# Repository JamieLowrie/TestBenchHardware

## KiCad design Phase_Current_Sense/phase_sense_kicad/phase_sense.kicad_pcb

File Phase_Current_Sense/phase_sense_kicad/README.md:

# 3-Channel Motor Phase Current + Voltage Sense — ACS37002 (KiCad 7 project), rev H — 4 layers

Open `phase_sense.kicad_pro` in KiCad 7, 8 or 9 (8/9 will offer to upgrade the files).

## What it is
- 3 × Allegro ACS37002LMABTR-066B3 (LCSC C3684355): ±66.7 A, 19.8 mV/A, 1.65 V = 0 A, 3.3 V supply
- 3 × phase-voltage dividers: 47k + 47k (C25819, two in series for voltage rating) / 2.7k (C13167) with 22 nF (C21122),
  tapped on the **motor side** of each sensor
- Each phase passes through two XFCN T44001 M4 solder terminals (LCSC C481447, 40 A, 4 legs): **IN (from drive) → sensor → OUT (to motor)**
- **4 layers**, board = CamdenBoss **CDIB/6/L2** lower PCB: 99.0 × 82.8 mm, 1 mm corner chamfers (from `CDIB-6ST-L2.STEP`)

## Layout — rev F
- The sensor circuit is pushed as far right as it goes. **The controller gets X < 53.6 mm** (dashed line on silk). Only J1
  and its little ground pad (X 47.4–55.3, Y 44–68.4, with Q1, R2, R3 and R4) stick over the line, as the interface.
- **Top-right window (Y < 10.5), from the middle outwards: DC− (J8, X 64.0), C IN 73.5, B IN 83.0, A IN 94.2.**
- **Bottom-right window (Y > 72.3): C OUT 65.5, B OUT 80.0, A OUT 94.2.**
- Each phase is one strip, C | B | A from left to right: IN terminal → sensor pins 1–4 (IP+) → pins 5–8 (IP−) → OUT terminal.
- **Layer use:**
  - **F.Cu / B.Cu:** phase copper on both layers, via-stitched, plus the small parts and GND.
  - **In1.Cu:** the LV signal wiring. It crosses under the phase strips only in a via-free band (Y 51.0–58.2).
  - **In2.Cu:** GND only. It sits under the LV areas, the crossing band, J1 and a strip from DC− down to J1. It is kept out from under the
    phase copper, so the phase dv/dt doesn't couple into GND.
- The A IN copper splits around the H2 pillar screw. It keeps 4 mm clear on top (under the screw head) and 2.4 mm clear on B.Cu.
  That still leaves about 5 mm on F.Cu and about 8.5 mm on B.Cu past the screw.

## Gain select — driven by the MCU
The GAIN_SEL pins of all three sensors are bussed and brought to J1:
- **GS0** goes to every sensor's GAIN_SEL_0 (pin 16), through R3 (10 kΩ).
- **GS1** goes to every sensor's GAIN_SEL_1 (pin 14), through R4 (10 kΩ).
- Inside each sensor there is a 1 MΩ pull-down, so a floating or reset GPIO gives **00**.

| GS1 / GS0 | Sensitivity | Range | Current per ADC count |
|---|---|---|---|
| 0 0 (default) | 19.8 mV/A | ±66.7 A | ~41 mA |
| 0 1 | 16.5 mV/A | ±80 A | ~49 mA |
| 1 0 | 13.2 mV/A | ±100 A | ~61 mA |
| 1 1 | 9.9 mV/A | ±133.3 A | ~81 mA |

**The ACS37002 only reads GAIN_SEL when it powers up**, so changing GS0/GS1 while it runs does nothing. To make a new
setting take effect, the board switches the sensors' supply:
- **Q1 (AO3401A, P-channel MOSFET)** feeds the sensors from +3V3 on a separate rail, **+3.3VA**.
- **R2** holds Q1 on, so the sensors run as soon as the board is powered.
- **SNS_OFF (J1 pin 13)**: drive it high to switch the sensors off.

Change the range from firmware like this:
1. Set GS0 / GS1 to the new code (push-pull outputs).
2. Drive SNS_OFF **high** for at least 10 ms. The sensors power down and +3.3VA falls below the power-on-reset level.
3. Drive SNS_OFF **low**. The sensors restart and latch the new GAIN_SEL.
4. Wait about 1 ms, then re-measure the zero-current offset and change the firmware scale.
5. Ignore FAULT_N and the ADC readings while the sensors are off (FAULT_N reads low then).

The overcurrent trip set by the VOC divider is a fraction of the selected range, so it moves up with the range. Check the
ACS37002 datasheet's VOC equation if you rely on FAULT_N at the higher ranges.

Why R3/R4 are there: while +3.3VA is off, a GPIO held high would feed the sensors through their input protection diodes.
That could stop them resetting properly. 10 kΩ limits it to a fraction of a milliamp. At 3.3 V the pin still sees about 3.2 V,
well above the 2.25 V logic-high threshold.

The VOC overcurrent trip divider and the FAULT_N pull-up sit on +3.3VA. Q1 drops about 3 mV, which slightly offsets the
ratiometric output (3.3 V seen by the MCU's ADC vs. ~3.297 V at the sensors). The firmware zero-calibration absorbs it.

## Current sign
Drive → motor current enters IP+, so it reads **positive**: `I = (adc − zero) × (3.3 / 4096) / 0.0198` → ≈ 40.7 mA/count.

## J1 – interface header (2.54 mm, 2×7) at X 51.0 / 53.54, Y 50.6–65.8
Wire these nets to the CH32V203 on your controller layout, or keep J1 as a header. Pin 1 is the square pad (top-left);
odd pins in the left column, even pins in the right. The pinout is printed on the back.

| Pin | Signal | Notes |
|---|---|---|
| 1 | 3V3 | MCU 3.3 V in. Same rail as MCU VDDA (the current output is ratiometric). Feeds the sensors through Q1 |
| 2 | IA | Phase A current, RC-filtered (1 kΩ / 10 nF, fc ≈ 16 kHz) → ADC |
| 3 | IB | Phase B current → ADC |
| 4 | IC | Phase C current → ADC |
| 5 | VA | Phase A voltage (÷35.8, fc ≈ 2.8 kHz) → ADC |
| 6 | VB | Phase B voltage → ADC |
| 7 | VC | Phase C voltage → ADC |
| 8 | FAULT_N | Open-drain wired-OR of all three OCF pins, 10 k pull-up to +3.3VA, active low (~77 A at the default range) |
| 9, 10, 14 | GND | |
| 11 | GS0 | GAIN_SEL_0 of all three sensors (GPIO out) |
| 12 | GS1 | GAIN_SEL_1 of all three sensors (GPIO out) |
| 13 | SNS_OFF | High = sensors off (GPIO out). Low or floating = sensors on |

Voltage: `V = adc × (3.3 / 4096) × (96.7 / 2.7)` → ≈ 28.9 mV/count, 118 V full scale (100 V → 2.79 V).

## J8 – drive DC− link (required for VA/VB/VC)
Phase voltage is measured relative to the drive's DC−. Bolt J8 to the drive's DC− with a short wire.
**This ties board GND (and your CH32V203, USB and debugger ground) to the drive's DC−**, so the board is not isolated
from the motor supply. Max bus voltage 100 V.

## Box fit (CDIB/6/L2), all in board coordinates (X right, Y down from the top window)
- **H1 (6.995, 66.405) and H2 (91.995, 16.405)**: Ø3.6 mm holes onto the two pillars, fixed with **No.6 self-tapping screws**.
- Terminal legs are only in the two open wiring strips (5.7 mm of space below the board there).
- **Centre platform, Y 21.5–61.2: only 0.5 mm below the PCB.** Everything there is SMD except **J1. Cut its legs flush**, or
  fit a surface-mount header.
- Box centre posts (X 45.7–53.2 at both ends) leave 3.3 mm above the board. Only flat copper is under them.
- About 19.5 mm from the PCB top to the roof: T44001 (8.4 mm) + ring lug + M4 pan head fits. Use ≤ 8 mm M4 screws.

## Spacing / creepage
- Custom DRC rule (`phase_sense.kicad_dru`): **every phase net keeps ≥ 0.5 mm from every other net**. That covers LV tracks, GND and the
  other phases (IPC-2221 B4, solder-masked, ≤ 100 V, with margin). Phase-to-phase copper gaps are 0.8 mm. The GND pour
  respects the rule when it is filled.
- The divider chains deliberately bridge HV to LV (47k + 47k), and J8 ties GND to DC−, so the board is **not** galvanically isolated.
- The ACS37002 package itself keeps ~7 mm between its HV and LV pins (1097 Vrms basic insulation working voltage).

## Known limitations — read before ordering
- **Current:** each sensor's primary is 0.85 mΩ, so 60 A DC ≈ 3 W per chip, which is too much for SOIC-16 continuously.
  **~30 A RMS per phase is the practical continuous limit. Order 2 oz outer copper.** The narrowest spot is A IN past
  the H2 screw (about 5 mm on F.Cu plus 8.5 mm on B.Cu).
- **Field coupling:** each phase's own OUT copper runs down right beside its sensor, and the next phase is one strip away.
  The ACS37002 rejects uniform external fields, but check each channel once against a clamp meter. If it is off by more than ~1 %,
  store a per-channel gain in firmware.

## Ordering at JLCPCB
1. Upload `fab/gerbers_JLCPCB.zip`. **4 layers, 1.6 mm, 2 oz outer copper** (the inner layers can stay at 0.5 oz; they carry no phase current).
2. PCB Assembly, top side: upload `fab/BOM_JLCPCB.csv` + `fab/CPL_JLCPCB.csv`.
3. **Check U1–U3 rotation in JLC's placement preview**: the pin-1 dot must be top-left, toward the IN terminals.
   KiCad and JLC sometimes disagree on SOIC rotation; fix it in the preview if needed.
4. J2–J8 (T44001) are through-hole. Either use JLC THT assembly, or remove them from the BOM and hand-solder with a big iron
   (≥ 80 W). The pours sink a lot of heat.
5. J1 is not in the BOM. Fit it yourself and trim the legs flush (see box notes).

## Verification done
- Schematic netlist cross-checked against the design (129 pins, 0 errors).
- PCB DRC: 0 unconnected, 0 clearance, 0 courtyard errors, with the 0.5 mm phase rule active. The only remaining entries are
  "library not in configuration" warnings from the headless build machine.
- Every PCB pad net and footprint matches the schematic (0 mismatches).

`gen/` holds the Python scripts that generated everything (`run.sh` = place + autoroute + DRC, `fab.py` = outputs).

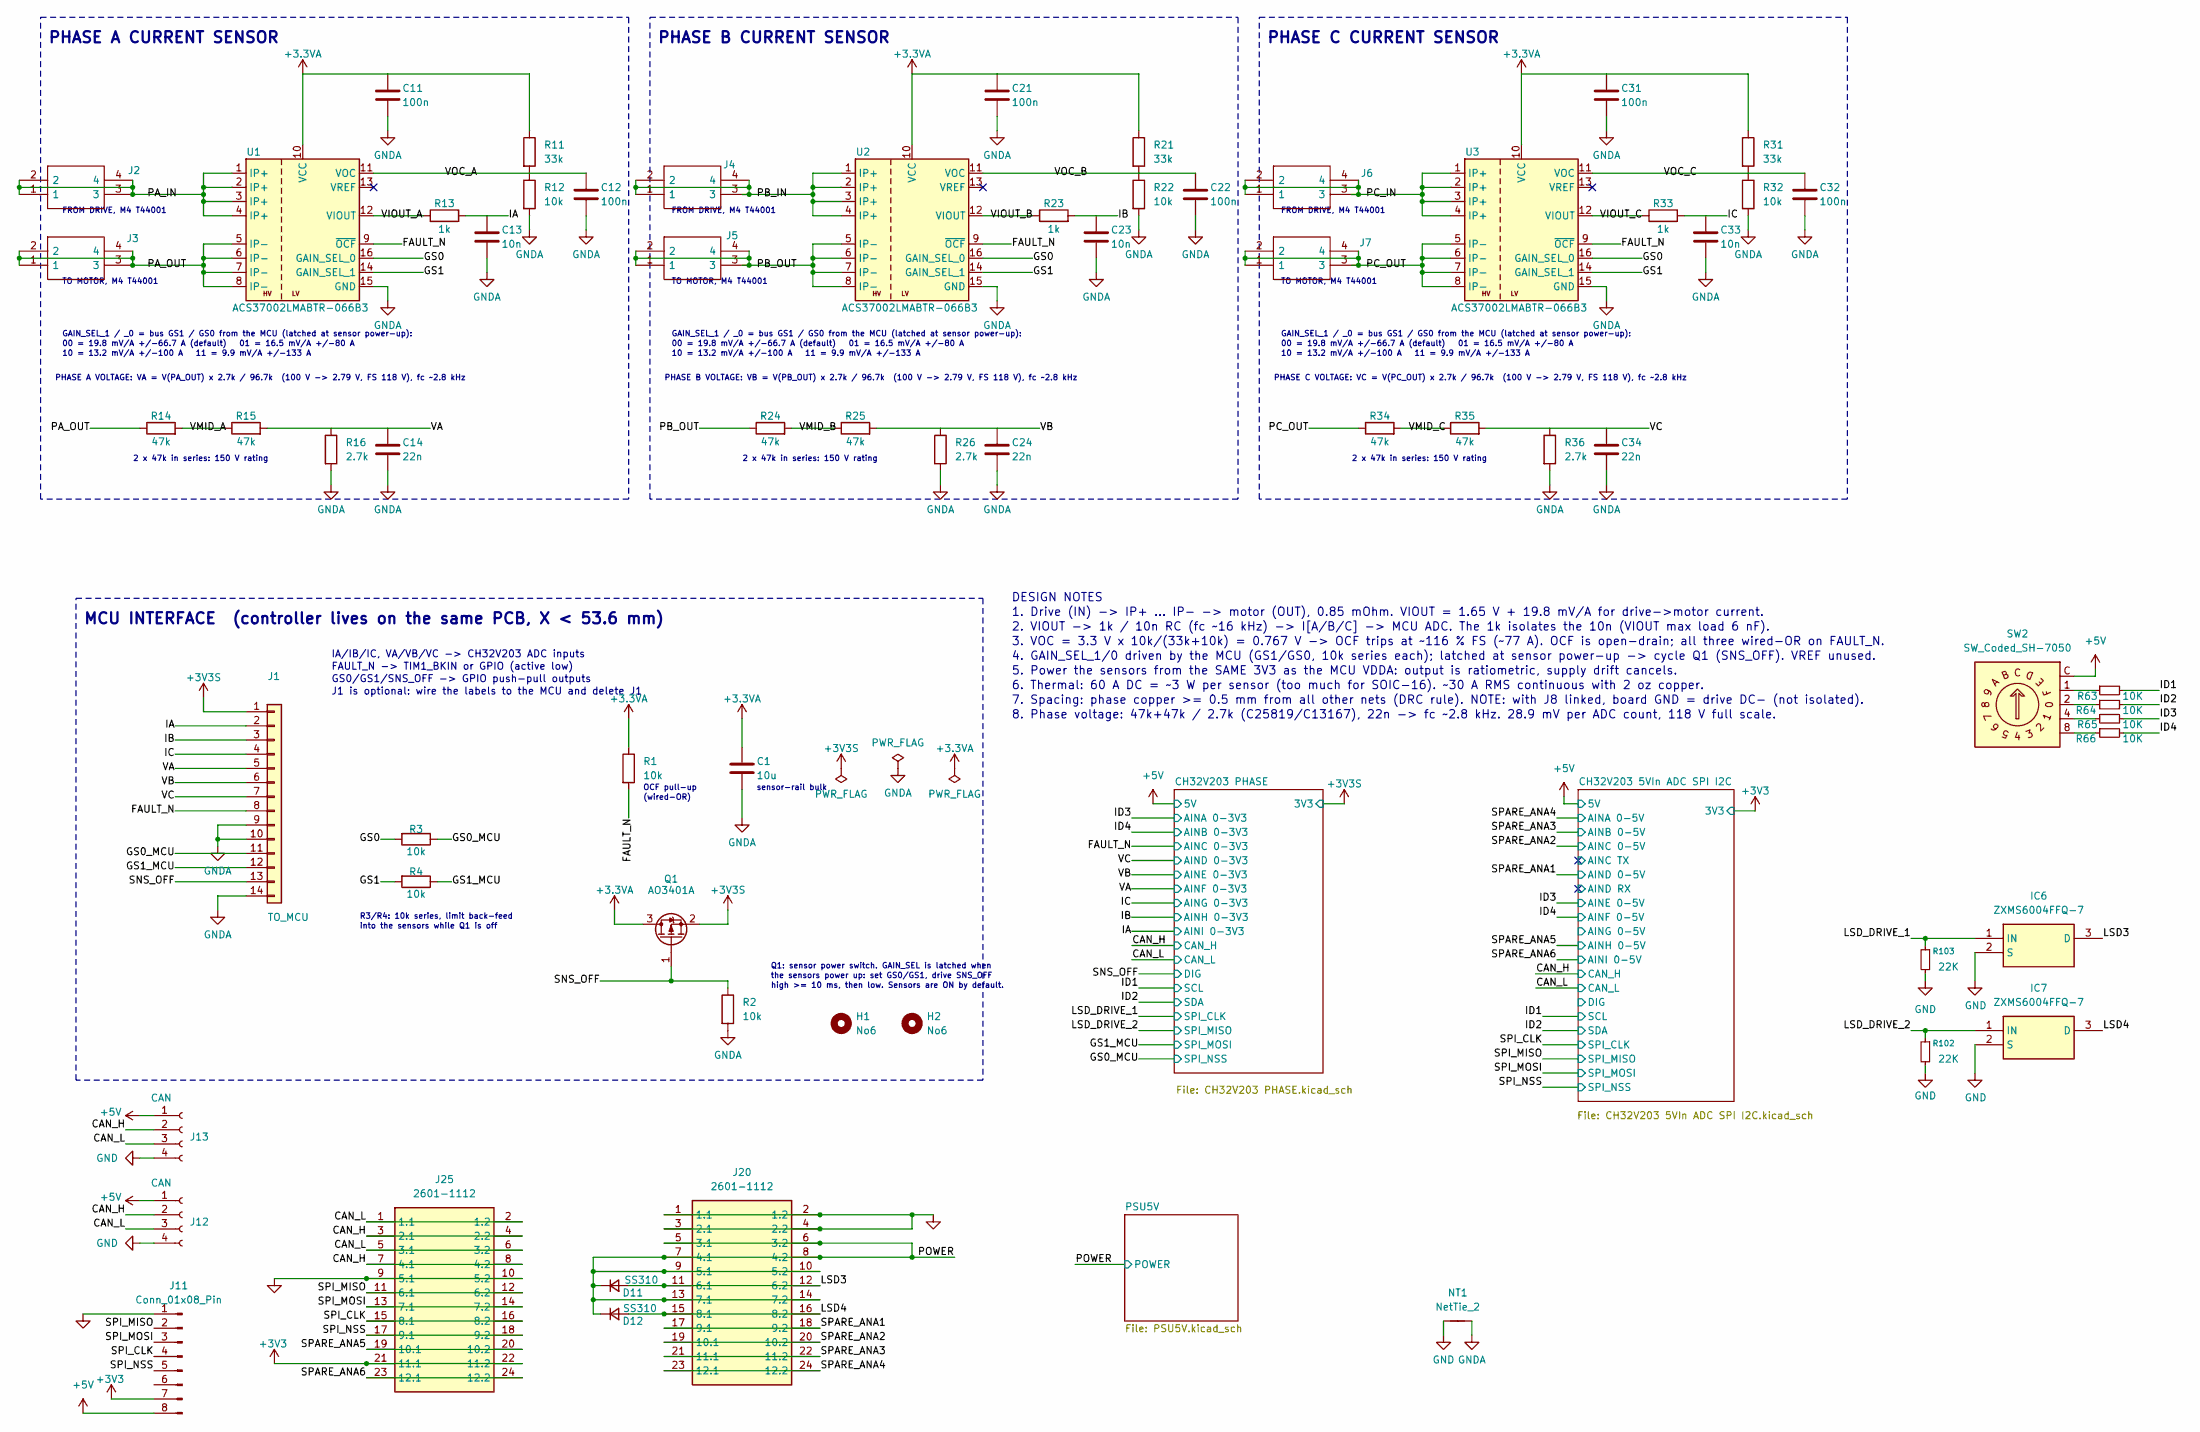
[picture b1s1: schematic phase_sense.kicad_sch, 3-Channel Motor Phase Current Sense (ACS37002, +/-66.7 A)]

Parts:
C1: 10u; C_0603_1608Metric; LCSC C19702
C11, C12, C21, C22, C31, C32: 100n; C_0603_1608Metric; LCSC C14663
C13, C23, C33: 10n; C_0603_1608Metric; LCSC C57112
C14, C24, C34: 22n; C_0603_1608Metric; LCSC C21122
D11, D12: SS310; D_SMA; LCSC DESCRIPTION 100V 3A Schottky Diode, SMA
H1, H2: No6; CDIB_Pillar_No6_Screw
IC6, IC7: ZXMS6004FFQ-7; SOTFL95P240X110-3N; Manufacturer_Part_Number ZXMS6004FFQ-7; Mouser Part Number 621-ZXMS6004FFQ-7
J1: TO_MCU; PinHeader_2x07_P2.54mm_Vertical
J2, J3, J4, J5, J6, J7: AMT0440007DB0000G; Manufacturer_Part_Number AMT0440007DB0000G; Mouser Part Number 523-AMT0440007DB000G
J11: Conn_01x08_Pin; JST_GH_BM09B-GHS-TBT_1x09-1MP_P1.25mm_Vertical; LCSC DNF
J12, J13: CAN; JST_GH_BM04B-GHS-TBT_1x04-1MP_P1.25mm_Vertical; LCSC DNF
J20, J25: 2601-1112; 26011112; Manufacturer_Part_Number 2601-1112
NT1: NetTie_2; NetTie-2_THT_Pad1.0mm
Q1: AO3401A; SOT-23; LCSC C15127
R1, R2, R3, R4, R12, R22, R32: 10k; R_0603_1608Metric; LCSC C25804
R11, R21, R31: 33k; R_0603_1608Metric; LCSC C4216
R13, R23, R33: 1k; R_0603_1608Metric; LCSC C21190
R14, R15, R24, R25, R34, R35: 47k; R_0603_1608Metric; LCSC C25819
R16, R26, R36: 2.7k; R_0603_1608Metric; LCSC C13167
R63, R64, R65, R66: 10K; R_0402_1005Metric; Manufacturer_Part_Number 0402WGF1002TCE; LCSC Description 62.5mW Thick Film Resistors 50V ±100ppm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
R102, R103: 22K; R_0402_1005Metric; LCSC C25768
SW2: SW_Coded_SH-7050; Nidec_Copal_SH-7010B; LCSC C5183894
U1, U2, U3: ACS37002LMABTR-066B3; SOIC-16W_7.5x10.3mm_P1.27mm; LCSC C3684355

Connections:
+3.3VA: C1.1, C11.1, C21.1, C31.1, Q1.3 (D), R1.1, R11.1, R21.1, R31.1, U1.10 (VCC), U2.10 (VCC), U3.10 (VCC)
+3V3: J11.7, J25.21 (11.1), J25.22 (11.2); also elsewhere on the board
+3V3S: J1.1, Q1.2 (S); also elsewhere on the board
+5V: J11.8, J12.1, J13.1, SW2.C; also elsewhere on the board
/CAN_H: J12.2, J13.2, J25.3 (2.1), J25.4 (2.2), J25.7 (4.1), J25.8 (4.2); also elsewhere on the board
/CAN_L: J12.3, J13.3, J25.1 (1.1), J25.2 (1.2), J25.5 (3.1), J25.6 (3.2); also elsewhere on the board
/FAULT_N: J1.8, R1.2, U1.9 (~OCF), U2.9 (~OCF), U3.9 (~OCF); also elsewhere on the board
/GS0: R3.2, U1.16 (GAIN_SEL_0), U2.16 (GAIN_SEL_0), U3.16 (GAIN_SEL_0)
/GS0_MCU: J1.11, R3.1; also elsewhere on the board
/GS1: R4.2, U1.14 (GAIN_SEL_1), U2.14 (GAIN_SEL_1), U3.14 (GAIN_SEL_1)
/GS1_MCU: J1.12, R4.1; also elsewhere on the board
/IA: C13.1, J1.2, R13.2; also elsewhere on the board
/IB: C23.1, J1.3, R23.2; also elsewhere on the board
/IC: C33.1, J1.4, R33.2; also elsewhere on the board
/ID1: R63.2; also elsewhere on the board
/ID2: R64.2; also elsewhere on the board
/ID3: R65.2; also elsewhere on the board
/ID4: R66.2; also elsewhere on the board
/LSD3: D11.2 (A), IC6.3 (D), J20.11 (6.1), J20.12 (6.2)
/LSD4: D12.2 (A), IC7.3 (D), J20.15 (8.1), J20.16 (8.2)
/LSD_DRIVE_1: IC6.1 (IN), R103.1; also elsewhere on the board
/LSD_DRIVE_2: IC7.1 (IN), R102.1; also elsewhere on the board
/PA_IN: J2.1, J2.2, J2.3, J2.4, U1.1 (IP+), U1.2 (IP+), U1.3 (IP+), U1.4 (IP+)
/PA_OUT: J3.1, J3.2, J3.3, J3.4, R14.1, U1.5 (IP-), U1.6 (IP-), U1.7 (IP-), U1.8 (IP-)
/PB_IN: J4.1, J4.2, J4.3, J4.4, U2.1 (IP+), U2.2 (IP+), U2.3 (IP+), U2.4 (IP+)
/PB_OUT: J5.1, J5.2, J5.3, J5.4, R24.1, U2.5 (IP-), U2.6 (IP-), U2.7 (IP-), U2.8 (IP-)
/PC_IN: J6.1, J6.2, J6.3, J6.4, U3.1 (IP+), U3.2 (IP+), U3.3 (IP+), U3.4 (IP+)
/PC_OUT: J7.1, J7.2, J7.3, J7.4, R34.1, U3.5 (IP-), U3.6 (IP-), U3.7 (IP-), U3.8 (IP-)
/POWER: D11.1 (K), D12.1 (K), J20.5 (3.1), J20.6 (3.2), J20.7 (4.1), J20.8 (4.2), J20.9 (5.1), J20.10 (5.2), J20.13 (7.1), J20.14 (7.2); also elsewhere on the board
/SNS_OFF: J1.13, Q1.1 (G), R2.1; also elsewhere on the board
/SPARE_ANA1: J20.17 (9.1), J20.18 (9.2); also elsewhere on the board
/SPARE_ANA2: J20.19 (10.1), J20.20 (10.2); also elsewhere on the board
/SPARE_ANA3: J20.21 (11.1), J20.22 (11.2); also elsewhere on the board
/SPARE_ANA4: J20.23 (12.1), J20.24 (12.2); also elsewhere on the board
/SPARE_ANA5: J25.19 (10.1), J25.20 (10.2); also elsewhere on the board
/SPARE_ANA6: J25.23 (12.1), J25.24 (12.2); also elsewhere on the board
/SPI_CLK: J11.4, J25.15 (8.1), J25.16 (8.2); also elsewhere on the board
/SPI_MISO: J11.2, J25.11 (6.1), J25.12 (6.2); also elsewhere on the board
/SPI_MOSI: J11.3, J25.13 (7.1), J25.14 (7.2); also elsewhere on the board
/SPI_NSS: J11.5, J25.17 (9.1), J25.18 (9.2); also elsewhere on the board
/VA: C14.1, J1.5, R15.2, R16.1; also elsewhere on the board
/VB: C24.1, J1.6, R25.2, R26.1; also elsewhere on the board
/VC: C34.1, J1.7, R35.2, R36.1; also elsewhere on the board
/VIOUT_A: R13.1, U1.12 (VIOUT)
/VIOUT_B: R23.1, U2.12 (VIOUT)
/VIOUT_C: R33.1, U3.12 (VIOUT)
/VMID_A: R14.2, R15.1
/VMID_B: R24.2, R25.1
/VMID_C: R34.2, R35.1
/VOC_A: C12.1, R11.2, R12.1, U1.11 (VOC)
/VOC_B: C22.1, R21.2, R22.1, U2.11 (VOC)
/VOC_C: C32.1, R31.2, R32.1, U3.11 (VOC)
GND: IC6.2 (S), IC7.2 (S), J11.1, J12.4, J13.4, J20.1 (1.1), J20.2 (1.2), J20.3 (2.1), J20.4 (2.2), J25.9 (5.1), J25.10 (5.2), NT1.1, R102.2, R103.2; also elsewhere on the board
GNDA: C1.2, C11.2, C12.2, C13.2, C14.2, C21.2, C22.2, C23.2, C24.2, C31.2, C32.2, C33.2, C34.2, J1.9, J1.10, J1.14, NT1.2, R2.2, R12.2, R16.2, R22.2, R26.2, R32.2, R36.2, U1.15 (GND), U2.15 (GND), U3.15 (GND); also elsewhere on the board
unnamed: R63.1, SW2.1
unnamed: R64.1, SW2.2
unnamed: R65.1, SW2.4
unnamed: R66.1, SW2.8

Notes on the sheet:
00 = 19.8 mV/A +/-66.7 A (default) 01 = 16.5 mV/A +/-80 A
PHASE C VOLTAGE: VC = V(PC_OUT) x 2.7k / 96.7k (100 V -> 2.79 V, FS 118 V), fc ~2.8 kHz
2. VIOUT -> 1k / 10n RC (fc ~16 kHz) -> I[A/B/C] -> MCU ADC. The 1k isolates the 10n (VIOUT max load 6 nF).
3. VOC = 3.3 V x 10k/(33k+10k) = 0.767 V -> OCF trips at ~116 % FS (~77 A). OCF is open-drain; all three wired-OR on FAULT_N.
IA/IB/IC, VA/VB/VC -> CH32V203 ADC inputs
GS0/GS1/SNS_OFF -> GPIO push-pull outputs
10 = 13.2 mV/A +/-100 A 11 = 9.9 mV/A +/-133 A
TO MOTOR, M4 T44001
5. Power the sensors from the SAME 3V3 as the MCU VDDA: output is ratiometric, supply drift cancels.
FAULT_N -> TIM1_BKIN or GPIO (active low)
PHASE C CURRENT SENSOR
GAIN_SEL_1 / _0 = bus GS1 / GS0 from the MCU (latched at sensor power-up):
1. Drive (IN) -> IP+ ... IP- -> motor (OUT), 0.85 mOhm. VIOUT = 1.65 V + 19.8 mV/A for drive->motor current.
PHASE B CURRENT SENSOR
R3/R4: 10k series, limit back-feed
2 x 47k in series: 150 V rating
DESIGN NOTES
MCU INTERFACE (controller lives on the same PCB, X < 53.6 mm)
PHASE A CURRENT SENSOR
8. Phase voltage: 47k+47k / 2.7k (C25819/C13167), 22n -> fc ~2.8 kHz. 28.9 mV per ADC count, 118 V full scale.
Q1: sensor power switch. GAIN_SEL is latched when
the sensors power up: set GS0/GS1, drive SNS_OFF
PHASE B VOLTAGE: VB = V(PB_OUT) x 2.7k / 96.7k (100 V -> 2.79 V, FS 118 V), fc ~2.8 kHz
OCF pull-up
(wired-OR)
6. Thermal: 60 A DC = ~3 W per sensor (too much for SOIC-16). ~30 A RMS continuous with 2 oz copper.
FROM DRIVE, M4 T44001
sensor-rail bulk
7. Spacing: phase copper >= 0.5 mm from all other nets (DRC rule). NOTE: with J8 linked, board GND = drive DC- (not isolated).
4. GAIN_SEL_1/0 driven by the MCU (GS1/GS0, 10k series each); latched at sensor power-up -> cycle Q1 (SNS_OFF). VREF unused.
J1 is optional: wire the labels to the MCU and delete J1
high >= 10 ms, then low. Sensors are ON by default.
into the sensors while Q1 is off
PHASE A VOLTAGE: VA = V(PA_OUT) x 2.7k / 96.7k (100 V -> 2.79 V, FS 118 V), fc ~2.8 kHz

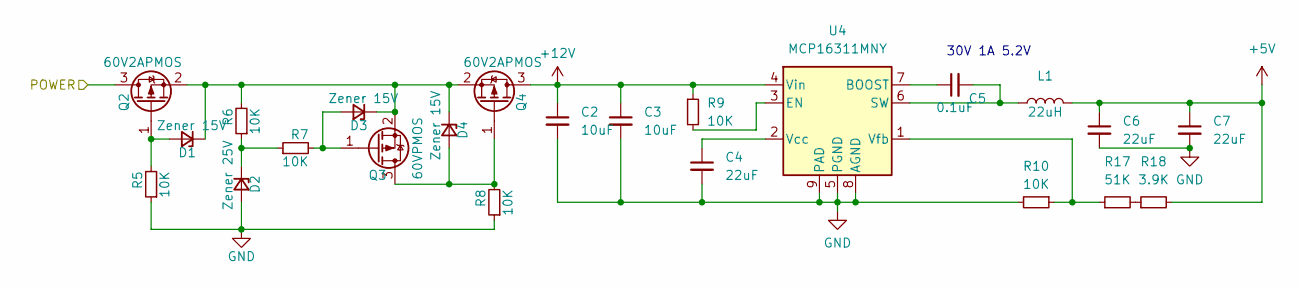
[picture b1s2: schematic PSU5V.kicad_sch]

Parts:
C2, C3: 10uF; C_0805_2012Metric; Manufacturer_Part_Number CL21A106KAYNNNE; LCSC Description 25V 10uF X5R ±10% 0805 Multilayer Ceram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
C4, C6, C7: 22uF; C_0603_1608Metric; LCSC Description 6.3V 22uF X5R ±20% 0603 Multilayer Cera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
C5: 0.1uF; C_0402_1005Metric; Manufacturer_Part_Number CL05B104KO5NNNC; LCSC Description 16V 100nF X7R ±10% 0402 Multilayer Cera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
D1, D3, D4: Zener 15V; D_SOD-523; MPN BZT52C15S-7-F; LCSC Description ±5% 300mW 15V SOD-523 Zener Diode
D2: Zener 25V; D_SOD-523; MPN DESCRIPTION 22.8V~25.6V 200mW 24.2V SOD-523 Zener D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; LCSC Description ±5% 300mW 15V SOD-523 Zener Diode
L1: 22uH; L_Vishay_IFSC-1515AH_4x4x1.8mm; LCSC Description 1A 22uH 磁胶屏蔽绕线电感 ±20% 1.3A SMD,4x4mm Po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
Q2, Q4: 60V2APMOS; SOT95P230X110-3N; Mouser Part Number 771-PMV28XPEAR
Q3: 60VPMOS; SOT95P230X110-3N; Mouser Part Number 771-PMV28XPEAR
R5, R6, R7, R8, R9, R10: 10K; R_0402_1005Metric; Manufacturer_Part_Number 0402WGF1002TCE; LCSC Description 62.5mW Thick Film Resistors 50V ±100ppm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
R17: 51K; R_0402_1005Metric; Manufacturer_Part_Number 0402WGF5102TCE; LCSC Description 62.5mW Thick Film Resistors 50V ±100ppm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
R18: 3.9K; R_0402_1005Metric; Manufacturer_Part_Number 0402WGF3901TCE; LCSC Description 62.5mW Thick Film Resistors 50V ±100ppm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
U4: MCP16311MNY; DFN-8-1EP_3x2mm_P0.5mm_EP1.75x1.45mm; JLCPCB MPN Step-down type Adjustable 4.4V~30V 1A 2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

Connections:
+5V: C6.1, C7.1, L1.2, R18.2; also elsewhere on the board
+12V: C2.1, C3.1, Q4.3 (D), R9.1, U4.4 (Vin)
/POWER: Q2.3 (D); also elsewhere on the board
GND: C2.2, C3.2, C4.2, C6.2, C7.2, D2.2 (A), R5.1, R8.1, R10.2, U4.5 (PGND), U4.8 (AGND), U4.9 (PAD); also elsewhere on the board
unnamed: D1.2 (A), Q2.1 (G), R5.2
unnamed: D1.1 (K), D3.1 (K), D4.1 (K), Q2.2 (S), Q3.2 (S), Q4.2 (S), R6.2
unnamed: D2.1 (K), R6.1, R7.1
unnamed: D3.2 (A), Q3.1 (G), R7.2
unnamed: D4.2 (A), Q3.3 (D), Q4.1 (G), R8.2
unnamed: R17.2, R18.1
unnamed: C5.1, U4.7 (BOOST)
unnamed: R9.2, U4.3 (EN)
unnamed: C5.2, L1.1, U4.6 (SW)
unnamed: C4.1, U4.2 (Vcc)
unnamed: R10.1, R17.1, U4.1 (Vfb)

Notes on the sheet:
30V 1A 5.2V

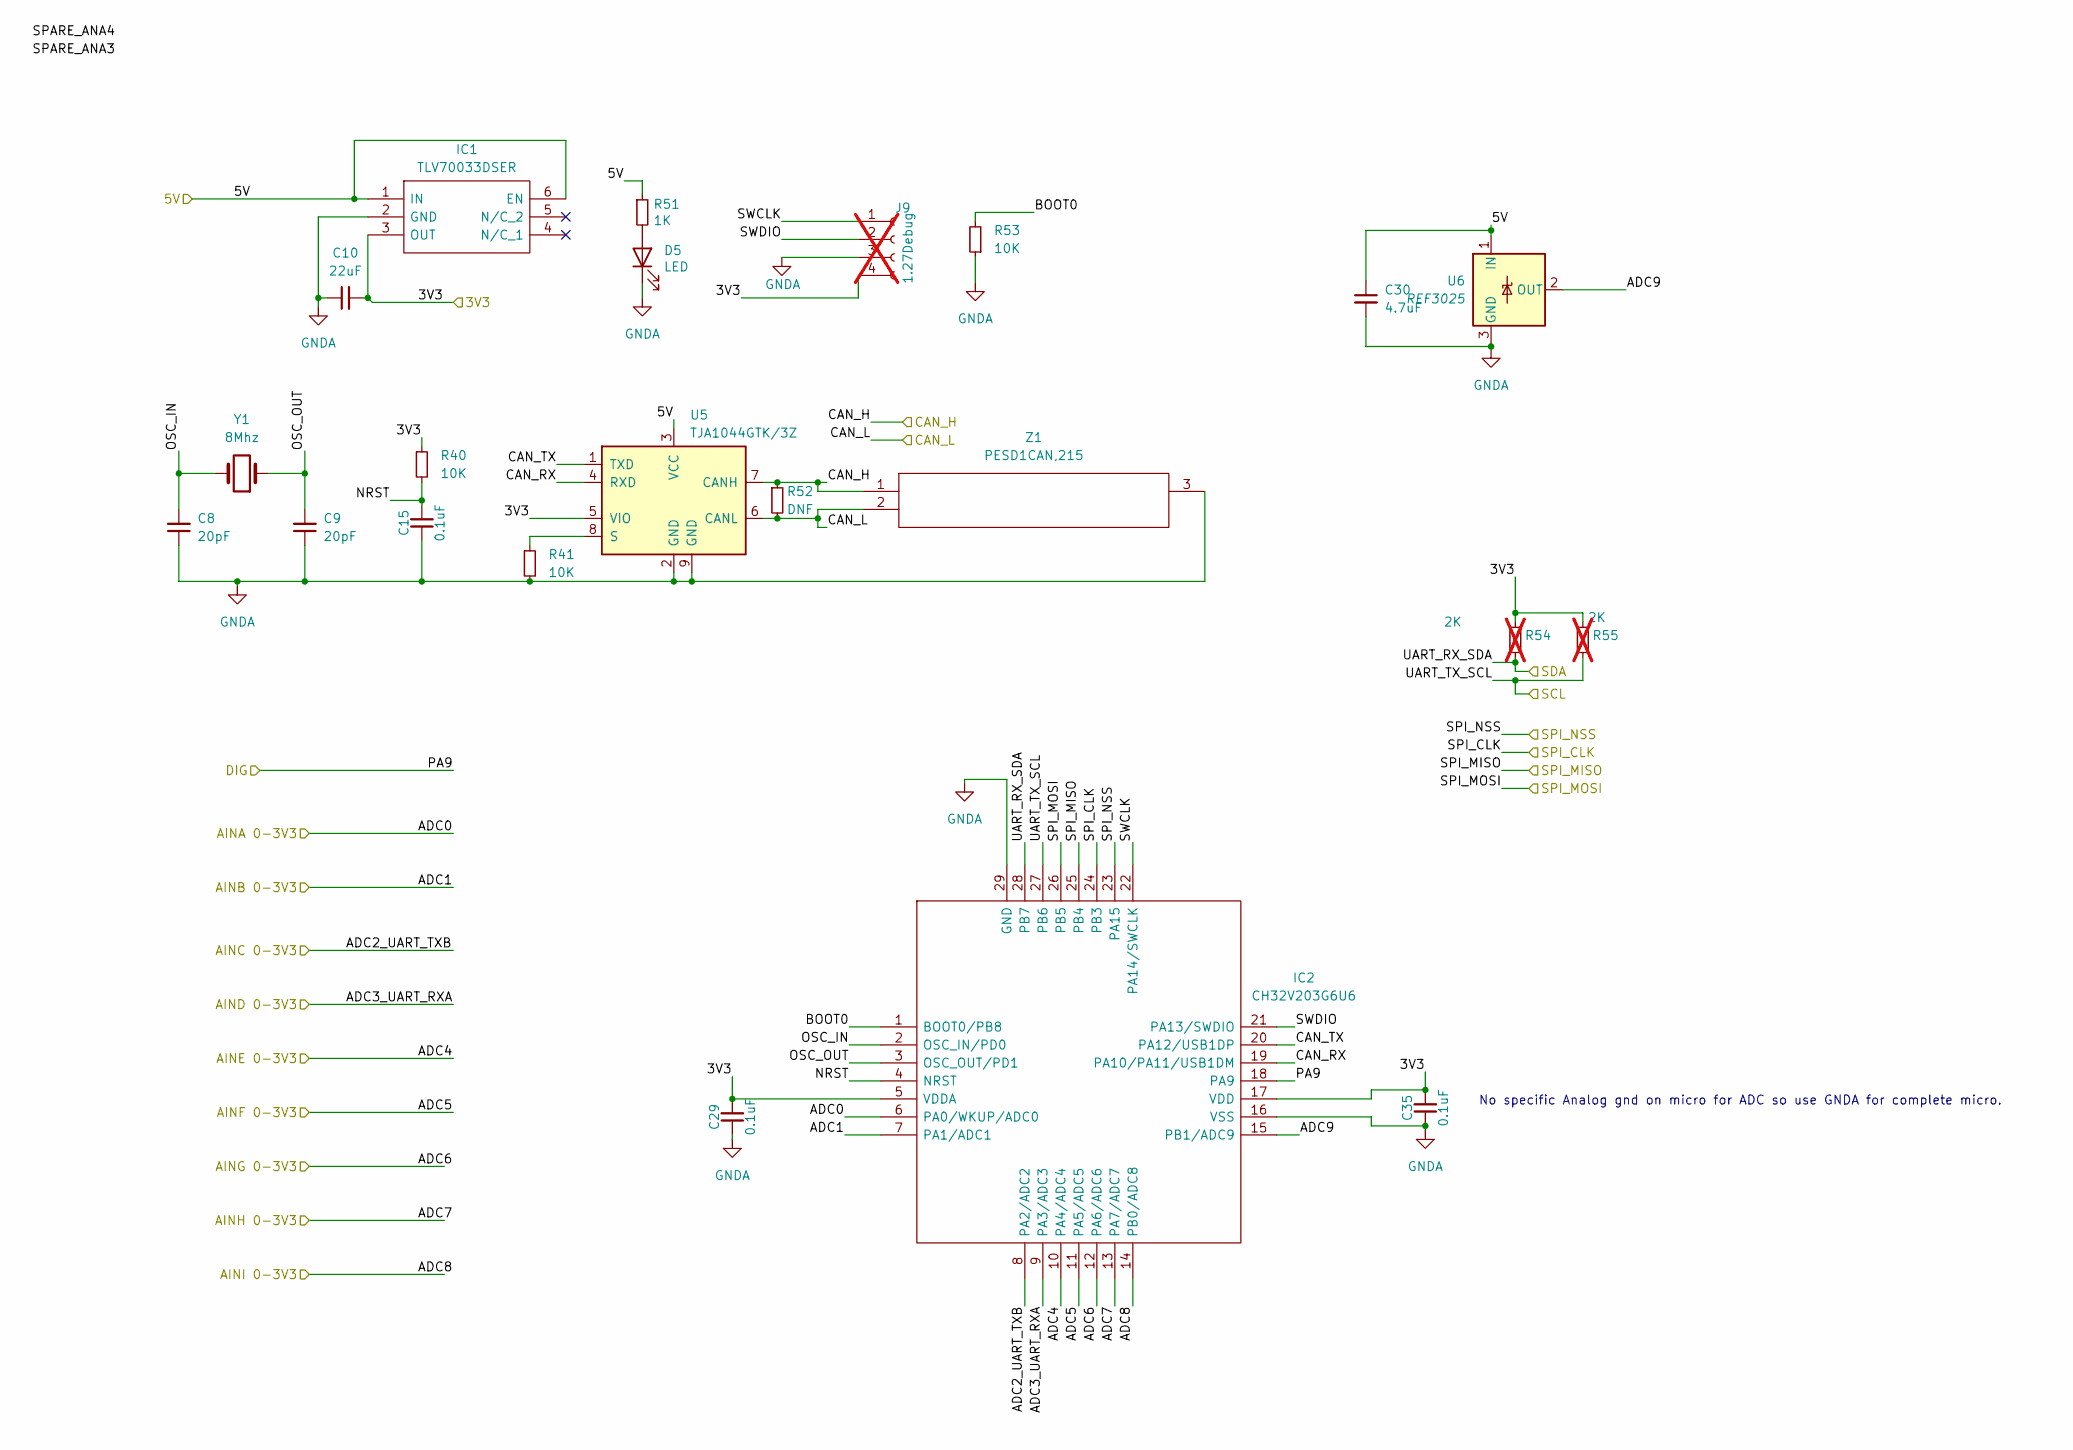
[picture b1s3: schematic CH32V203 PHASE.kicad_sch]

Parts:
C8, C9: 20pF; C_0402_1005Metric; Manufacturer_Part_Number 0402CG200J500NT; LCSC Description 50V 20pF C0G ±5% 0402 Multilayer Cerami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
C10: 22uF; C_0603_1608Metric; LCSC Description 6.3V 22uF X5R ±20% 0603 Multilayer Cera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
C15, C29, C35: 0.1uF; C_0402_1005Metric; Manufacturer_Part_Number CL05B104KO5NNNC; LCSC Description 16V 100nF X7R ±10% 0402 Multilayer Cera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
C30: 4.7uF; C_0603_1608Metric; LCSC C19666
D5: LED; LED_0603_1608Metric; LCSC Description -40℃~+85℃ Red 0603 Light Emitting Diode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
IC1: TLV70033DSER; SON50P150X150X80-6N; Mouser Part Number 595-TLV70033DSER
IC2: CH32V203G6U6; QFN40P400X400X80-29N-D; Manufacturer_Part_Number CH32V203G6U6; LCSC Description RISC-V QFN28X4 Microcontroller Units (M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
J9: 1.27Debug; PinHeader_1x04_P1.27mm_Vertical; LCSC C161692; not fitted
R40, R41, R53: 10K; R_0402_1005Metric; Manufacturer_Part_Number 0402WGF1002TCE; LCSC Description 62.5mW Thick Film Resistors 50V ±100ppm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
R51: 1K; R_0402_1005Metric; LCSC Description 62.5mW Thick Film Resistors 50V ±100ppm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
R52: DNF; R_0603_1608Metric; LCSC DNF
R54, R55: 2K; R_0402_1005Metric; LCSC Description 62.5mW Thick Film Resistors 50V ±100ppm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; not fitted
U5: TJA1044GTK/3Z; DFN-8-1EP_3x3mm_P0.65mm_EP1.55x2.4mm; LCSC Description HVSON-8-EP(3x3) CAN ICs ROHS
U6: REF3025; SOT-23; LCSC C11334
Y1: 8Mhz; Crystal_SMD_5032-2Pin_5.0x3.2mm; Manufacturer_Part_Number X50328MSB2GI; LCSC Description 20pF ±10ppm ±20ppm SMD5032 Crystals ROHS
Z1: PESD1CAN,215; SOT95P230X110-3N; Manufacturer_Part_Number PESD1CAN,215; Mouser Part Number 771-PESD1CAN-T/R

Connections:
+3V3S: C10.2, C29.2, C35.2, IC1.3 (OUT), IC2.5 (VDDA), IC2.17 (VDD), J9.4, R40.1, R54.1, R55.1, U5.5 (VIO); also elsewhere on the board
+5V: C30.1, IC1.1 (IN), IC1.6 (EN), R51.1, U5.3 (VCC), U6.1 (IN); also elsewhere on the board
/CAN_H: R52.1, U5.7 (CANH), Z1.1; also elsewhere on the board
/CAN_L: R52.2, U5.6 (CANL), Z1.2; also elsewhere on the board
/CH32V203 PHASE/ADC9: IC2.15 (PB1/ADC9), U6.2 (OUT)
/CH32V203 PHASE/BOOT0: IC2.1 (BOOT0/PB8), R53.2
/CH32V203 PHASE/CAN_RX: IC2.19 (PA10/PA11/USB1DM), U5.4 (RXD)
/CH32V203 PHASE/CAN_TX: IC2.20 (PA12/USB1DP), U5.1 (TXD)
/CH32V203 PHASE/NRST: C15.2, IC2.4 (NRST), R40.2
/CH32V203 PHASE/OSC_IN: C8.2, IC2.2 (OSC_IN/PD0), Y1.2
/CH32V203 PHASE/OSC_OUT: C9.2, IC2.3 (OSC_OUT/PD1), Y1.1
/CH32V203 PHASE/SWCLK: IC2.22 (PA14/SWCLK), J9.1
/CH32V203 PHASE/SWDIO: IC2.21 (PA13/SWDIO), J9.2
/FAULT_N: IC2.8 (PA2/ADC2); also elsewhere on the board
/GS0_MCU: IC2.23 (PA15); also elsewhere on the board
/GS1_MCU: IC2.26 (PB5); also elsewhere on the board
/IA: IC2.14 (PB0/ADC8); also elsewhere on the board
/IB: IC2.13 (PA7/ADC7); also elsewhere on the board
/IC: IC2.12 (PA6/ADC6); also elsewhere on the board
/ID1: IC2.27 (PB6), R55.2; also elsewhere on the board
/ID2: IC2.28 (PB7), R54.2; also elsewhere on the board
/ID3: IC2.6 (PA0/WKUP/ADC0); also elsewhere on the board
/ID4: IC2.7 (PA1/ADC1); also elsewhere on the board
/LSD_DRIVE_1: IC2.24 (PB3); also elsewhere on the board
/LSD_DRIVE_2: IC2.25 (PB4); also elsewhere on the board
/SNS_OFF: IC2.18 (PA9); also elsewhere on the board
/VA: IC2.11 (PA5/ADC5); also elsewhere on the board
/VB: IC2.10 (PA4/ADC4); also elsewhere on the board
/VC: IC2.9 (PA3/ADC3); also elsewhere on the board
GNDA: C8.1, C9.1, C10.1, C15.1, C29.1, C30.2, C35.1, D5.1 (K), IC1.2 (GND), IC2.16 (VSS), IC2.29 (GND), J9.3, R41.2, R53.1, U5.2 (GND), U5.9 (GND), U6.3 (GND), Z1.3; also elsewhere on the board
unnamed: D5.2 (A), R51.2
unnamed: R41.1, U5.8 (S)

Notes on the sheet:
No specific Analog gnd on micro for ADC so use GNDA for complete micro.

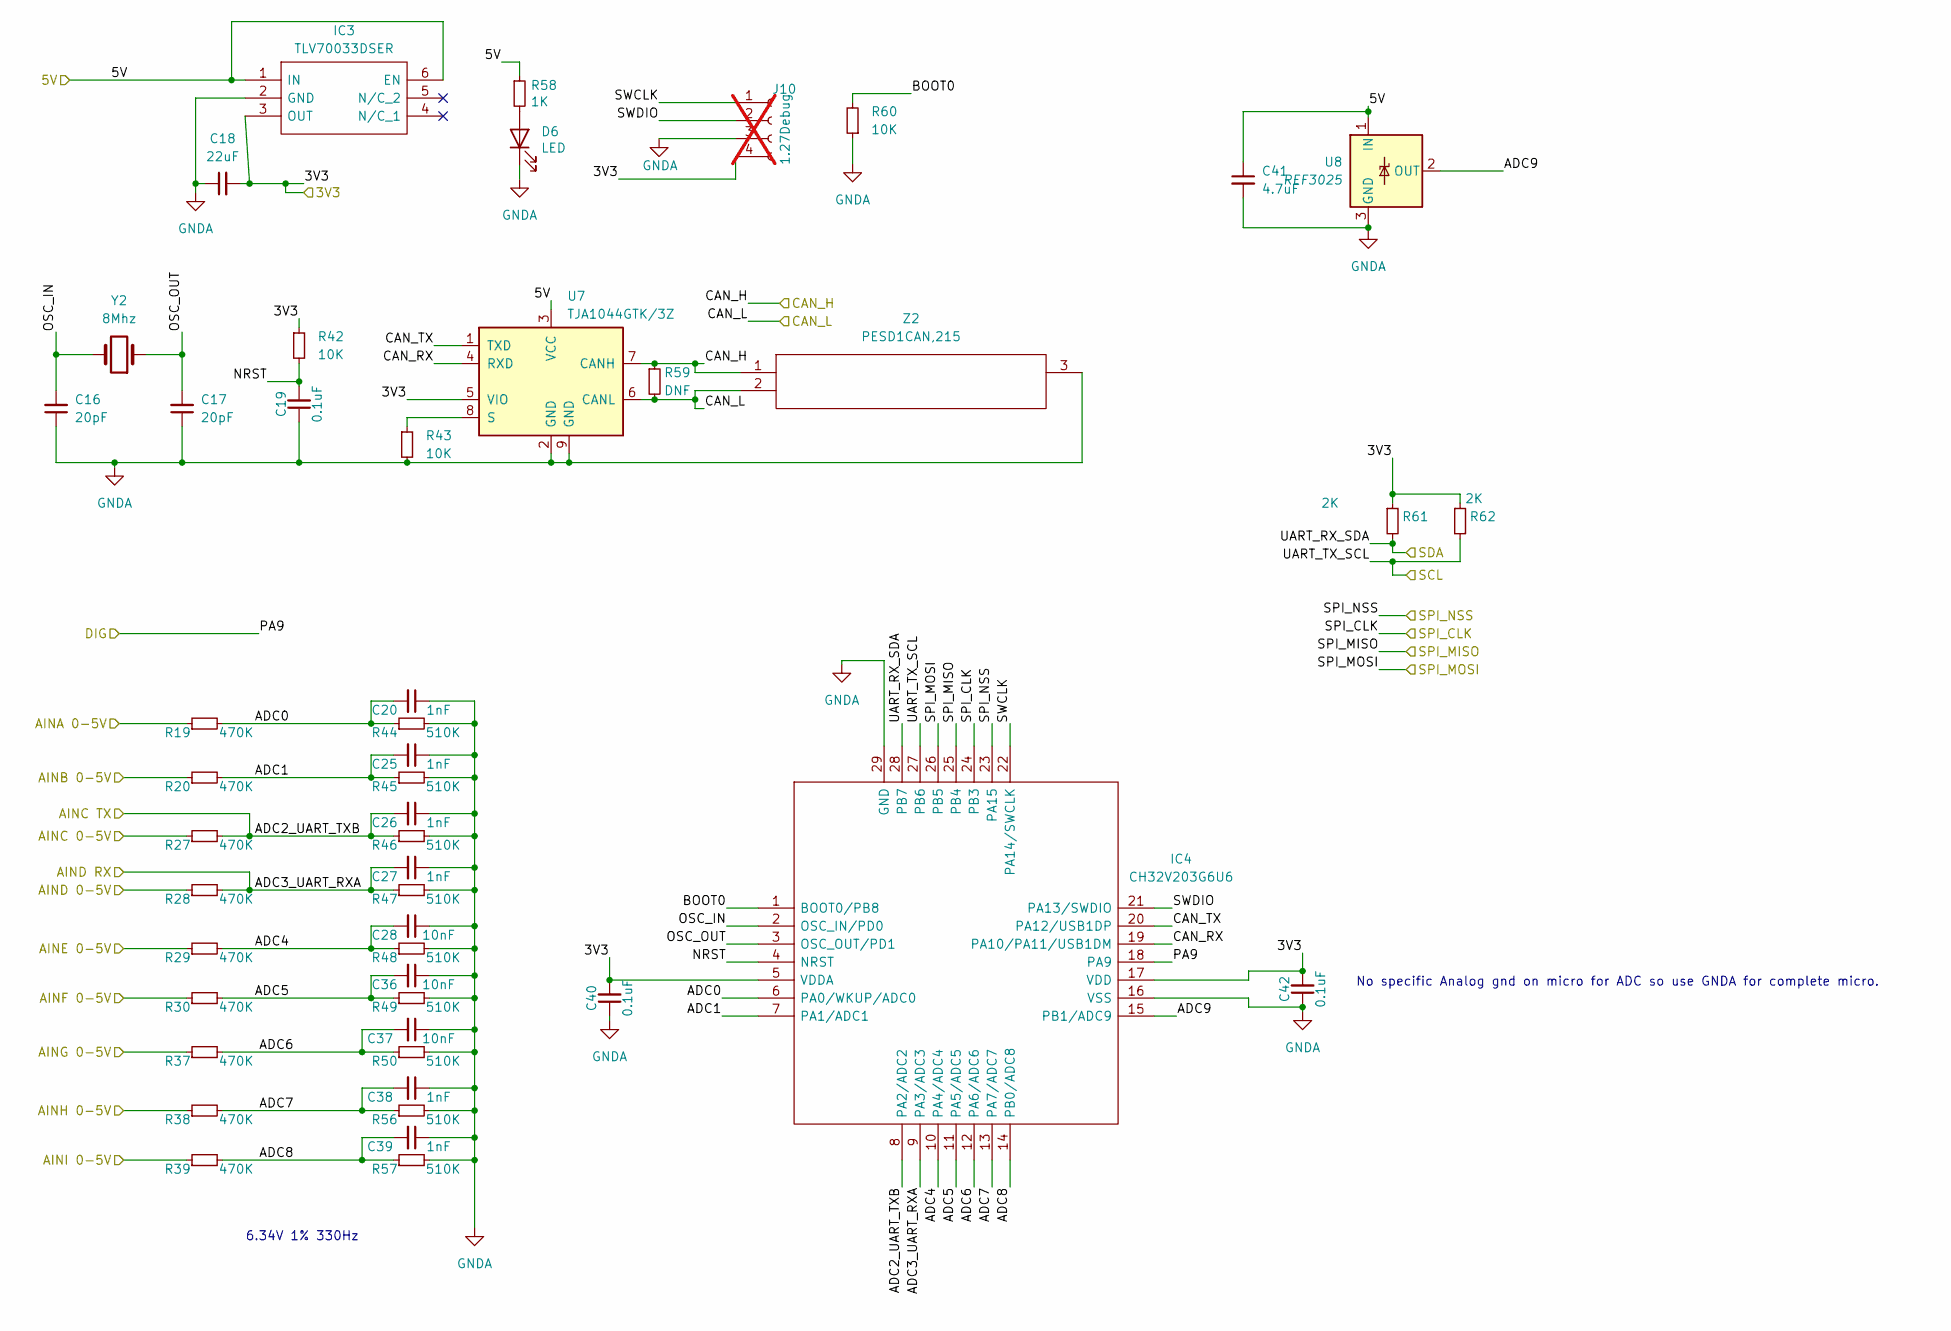
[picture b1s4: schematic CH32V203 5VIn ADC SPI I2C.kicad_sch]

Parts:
C16, C17: 20pF; C_0402_1005Metric; Manufacturer_Part_Number 0402CG200J500NT; LCSC Description 50V 20pF C0G ±5% 0402 Multilayer Cerami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
C18: 22uF; C_0603_1608Metric; LCSC Description 6.3V 22uF X5R ±20% 0603 Multilayer Cera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
C19, C40, C42: 0.1uF; C_0402_1005Metric; Manufacturer_Part_Number CL05B104KO5NNNC; LCSC Description 16V 100nF X7R ±10% 0402 Multilayer Cera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
C20, C25, C26, C27, C38, C39: 1nF; C_0402_1005Metric; LCSC Description 50V 1nF X7R ±10% 0402 Multilayer Cerami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
C28, C36, C37: 10nF; C_0402_1005Metric; Manufacturer_Part_Number 0402CG200J500NT; LCSC Description 50V 10nF X7R ±10% 0402 Multilayer Ceram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
C41: 4.7uF; C_0603_1608Metric; LCSC C19666
D6: LED; LED_0603_1608Metric; LCSC Description -40℃~+85℃ Red 0603 Light Emitting Diode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
IC3: TLV70033DSER; SON50P150X150X80-6N; Mouser Part Number 595-TLV70033DSER
IC4: CH32V203G6U6; QFN40P400X400X80-29N-D; Manufacturer_Part_Number CH32V203G6U6; LCSC Description RISC-V QFN28X4 Microcontroller Units (M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
J10: 1.27Debug; PinHeader_1x04_P1.27mm_Vertical; LCSC C161692; not fitted
R19, R20, R27, R28, R29, R30, R37, R38, R39: 470K; R_0402_1005Metric; Manufacturer_Part_Number 0402WGF1002TCE; LCSC Description 62.5mW Thick Film Resistors 50V ±100ppm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
R42, R43, R60: 10K; R_0402_1005Metric; Manufacturer_Part_Number 0402WGF1002TCE; LCSC Description 62.5mW Thick Film Resistors 50V ±100ppm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
R44, R45, R46, R47, R48, R49, R50, R56, R57: 510K; R_0402_1005Metric; Manufacturer_Part_Number 0402WGF1002TCE; LCSC Description 62.5mW Thick Film Resistors 50V ±100ppm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
R58: 1K; R_0402_1005Metric; LCSC Description 62.5mW Thick Film Resistors 50V ±100ppm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
R59: DNF; R_0603_1608Metric; LCSC DNF
R61, R62: 2K; R_0402_1005Metric; LCSC Description 62.5mW Thick Film Resistors 50V ±100ppm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
U7: TJA1044GTK/3Z; DFN-8-1EP_3x3mm_P0.65mm_EP1.55x2.4mm; LCSC Description HVSON-8-EP(3x3) CAN ICs ROHS
U8: REF3025; SOT-23; LCSC C11334
Y2: 8Mhz; Crystal_SMD_5032-2Pin_5.0x3.2mm; Manufacturer_Part_Number X50328MSB2GI; LCSC Description 20pF ±10ppm ±20ppm SMD5032 Crystals ROHS
Z2: PESD1CAN,215; SOT95P230X110-3N; Manufacturer_Part_Number PESD1CAN,215; Mouser Part Number 771-PESD1CAN-T/R

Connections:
+3V3: C18.2, C40.2, C42.2, IC3.3 (OUT), IC4.5 (VDDA), IC4.17 (VDD), J10.4, R42.1, R61.1, R62.1, U7.5 (VIO); also elsewhere on the board
+5V: C41.1, IC3.1 (IN), IC3.6 (EN), R58.1, U7.3 (VCC), U8.1 (IN); also elsewhere on the board
/CAN_H: R59.1, U7.7 (CANH), Z2.1; also elsewhere on the board
/CAN_L: R59.2, U7.6 (CANL), Z2.2; also elsewhere on the board
/CH32V203 5VIn ADC SPI I2C/ADC0: C20.2, IC4.6 (PA0/WKUP/ADC0), R19.2, R44.1
/CH32V203 5VIn ADC SPI I2C/ADC1: C25.2, IC4.7 (PA1/ADC1), R20.2, R45.1
/CH32V203 5VIn ADC SPI I2C/ADC2_UART_TXB: C26.2, IC4.8 (PA2/ADC2), R27.2, R46.1
/CH32V203 5VIn ADC SPI I2C/ADC3_UART_RXA: C27.2, IC4.9 (PA3/ADC3), R28.2, R47.1
/CH32V203 5VIn ADC SPI I2C/ADC4: C28.2, IC4.10 (PA4/ADC4), R29.2, R48.1
/CH32V203 5VIn ADC SPI I2C/ADC5: C36.2, IC4.11 (PA5/ADC5), R30.2, R49.1
/CH32V203 5VIn ADC SPI I2C/ADC6: C37.2, IC4.12 (PA6/ADC6), R37.2, R50.1
/CH32V203 5VIn ADC SPI I2C/ADC7: C38.2, IC4.13 (PA7/ADC7), R38.2, R56.1
/CH32V203 5VIn ADC SPI I2C/ADC8: C39.2, IC4.14 (PB0/ADC8), R39.2, R57.1
/CH32V203 5VIn ADC SPI I2C/ADC9: IC4.15 (PB1/ADC9), U8.2 (OUT)
/CH32V203 5VIn ADC SPI I2C/AING 0-5V: R37.1
/CH32V203 5VIn ADC SPI I2C/BOOT0: IC4.1 (BOOT0/PB8), R60.2
/CH32V203 5VIn ADC SPI I2C/CAN_RX: IC4.19 (PA10/PA11/USB1DM), U7.4 (RXD)
/CH32V203 5VIn ADC SPI I2C/CAN_TX: IC4.20 (PA12/USB1DP), U7.1 (TXD)
/CH32V203 5VIn ADC SPI I2C/NRST: C19.2, IC4.4 (NRST), R42.2
/CH32V203 5VIn ADC SPI I2C/OSC_IN: C16.2, IC4.2 (OSC_IN/PD0), Y2.2
/CH32V203 5VIn ADC SPI I2C/OSC_OUT: C17.2, IC4.3 (OSC_OUT/PD1), Y2.1
/CH32V203 5VIn ADC SPI I2C/PA9: IC4.18 (PA9)
/CH32V203 5VIn ADC SPI I2C/SWCLK: IC4.22 (PA14/SWCLK), J10.1
/CH32V203 5VIn ADC SPI I2C/SWDIO: IC4.21 (PA13/SWDIO), J10.2
/ID1: IC4.27 (PB6), R62.2; also elsewhere on the board
/ID2: IC4.28 (PB7), R61.2; also elsewhere on the board
/ID3: R29.1; also elsewhere on the board
/ID4: R30.1; also elsewhere on the board
/SPARE_ANA1: R28.1; also elsewhere on the board
/SPARE_ANA2: R27.1; also elsewhere on the board
/SPARE_ANA3: R20.1; also elsewhere on the board
/SPARE_ANA4: R19.1; also elsewhere on the board
/SPARE_ANA5: R38.1; also elsewhere on the board
/SPARE_ANA6: R39.1; also elsewhere on the board
/SPI_CLK: IC4.24 (PB3); also elsewhere on the board
/SPI_MISO: IC4.25 (PB4); also elsewhere on the board
/SPI_MOSI: IC4.26 (PB5); also elsewhere on the board
/SPI_NSS: IC4.23 (PA15); also elsewhere on the board
GNDA: C16.1, C17.1, C18.1, C19.1, C20.1, C25.1, C26.1, C27.1, C28.1, C36.1, C37.1, C38.1, C39.1, C40.1, C41.2, C42.1, D6.1 (K), IC3.2 (GND), IC4.16 (VSS), IC4.29 (GND), J10.3, R43.2, R44.2, R45.2, R46.2, R47.2, R48.2, R49.2, R50.2, R56.2, R57.2, R60.1, U7.2 (GND), U7.9 (GND), U8.3 (GND), Z2.3; also elsewhere on the board
unnamed: D6.2 (A), R58.2
unnamed: R43.1, U7.8 (S)

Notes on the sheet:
6.34V 1% 330Hz
No specific Analog gnd on micro for ADC so use GNDA for complete micro.

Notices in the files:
Voltage_Out/VoltageOut.kicad_pcb:
Voltage_Out V1.0 Copyright FooBarEngineering 2026
